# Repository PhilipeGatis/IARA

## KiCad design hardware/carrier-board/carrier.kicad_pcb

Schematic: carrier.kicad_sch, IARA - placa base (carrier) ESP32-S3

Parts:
BT1: CR2032; BatteryHolder_MYOUNG_BS-07-A1BJ001_CR2032; LCSC C2979167
C1: 470uF 25V; CP_Elec_10x10.5; LCSC C3445246
C2, C13, C16: 10uF 50V; C_1206_3216Metric; LCSC C13585
C3, C4, C9, C10, C14, C15, C17, C18, C19, C21, C22, C23, C24: 100nF; C_0603_1608Metric; LCSC C14663
C5, C6: 22uF 25V; C_1206_3216Metric; LCSC C12891
C7: 470uF 16V; CP_Elec_6.3x7.7; LCSC C2977552
C8: 1000uF 10V; CP_Elec_8x10.5; LCSC C48935400
C11, C12: 1uF; C_0603_1608Metric; LCSC C15849
C20: 100uF 16V; CP_Elec_6.3x5.4; LCSC C2887276
D1: SMBJ15A; D_SMB; LCSC C19077569
D2, D3, D5, D7, D9, D11, D13, D15, D17: SS34; D_SMA; LCSC C8678
D4, D6, D8, D10, D12, D14, D16, D18, D21: LED green; LED_0805_2012Metric; LCSC C2297
D19, D20, D22, D23: BAT54S; SOT-23; LCSC C7420333
F1, F2, F3, F4, F5, F6, F8, F9: PTC 0.75A hold; Fuse_1812_4532Metric; LCSC C369169
F7: PTC 0.5A hold; Fuse_1812_4532Metric; LCSC C369168
H1, H2, H3, H4: M3; MountingHole_3.2mm_M3
J1: 12V IN; TerminalBlock_Phoenix_MKDS-1,5-2-5.08_1x02_P5.08mm_Horizont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; LCSC C474952
J2: DevKit J1; PinSocket_1x22_P2.54mm_Vertical; LCSC C41376161
J3: DevKit J3; PinSocket_1x22_P2.54mm_Vertical; LCSC C41376161
J4: CH1 FERT1; TerminalBlock_Phoenix_PT-1,5-2-3.5-H_1x02_P3.50mm_Horizontal; LCSC C466970
J5: CH2 FERT2; TerminalBlock_Phoenix_PT-1,5-2-3.5-H_1x02_P3.50mm_Horizontal; LCSC C466970
J6: CH3 FERT3; TerminalBlock_Phoenix_PT-1,5-2-3.5-H_1x02_P3.50mm_Horizontal; LCSC C466970
J7: CH4 FERT4; TerminalBlock_Phoenix_PT-1,5-2-3.5-H_1x02_P3.50mm_Horizontal; LCSC C466970
J8: CH5 PRIME; TerminalBlock_Phoenix_PT-1,5-2-3.5-H_1x02_P3.50mm_Horizontal; LCSC C466970
J9: CH6 DRAIN; TerminalBlock_Phoenix_PT-1,5-2-3.5-H_1x02_P3.50mm_Horizontal; LCSC C466970
J10: CH7 REFILL; TerminalBlock_Phoenix_PT-1,5-2-3.5-H_1x02_P3.50mm_Horizontal; LCSC C466970
J11: CH8 SOLENOID; TerminalBlock_Phoenix_PT-1,5-2-3.5-H_1x02_P3.50mm_Horizontal; LCSC C466970
J12: REED; TerminalBlock_Phoenix_PT-1,5-2-3.5-H_1x02_P3.50mm_Horizontal; LCSC C466970
J13: SSR V SEL; PinHeader_1x03_P2.54mm_Vertical; LCSC C2894926
J14: SSR CANISTER; TerminalBlock_Phoenix_PT-1,5-3-3.5-H_1x03_P3.50mm_Horizontal; LCSC C474893
J15: CH9 PONTE H; TerminalBlock_Phoenix_PT-1,5-2-3.5-H_1x02_P3.50mm_Horizontal; LCSC C466970
J16: TFT ST7735; PinHeader_1x08_P2.54mm_Vertical; LCSC C492407
J17: BOTAO; PinHeader_1x02_P2.54mm_Vertical; LCSC C492401
J18: ULTRASSOM A02; PinHeader_1x04_P2.54mm_Vertical; LCSC C2691448
J19: BOIA; PinHeader_1x02_P2.54mm_Vertical; LCSC C492401
J20: I2C EXP; PinHeader_1x04_P2.54mm_Vertical; LCSC C2691448
L1: 4.7uH; L_Changjiang_FXL0630; LCSC C167220
Q1, Q2, Q3, Q4, Q5, Q6, Q7, Q8, Q9: AO3400A; SOT-23; LCSC C20917
Q10: AO4407A; SOIC-8_3.9x4.9mm_P1.27mm; LCSC C16072
R1, R4, R7, R10, R13, R16, R19, R22, R28, R37, R39, R41: 100R; R_0603_1608Metric; LCSC C22775
R2, R5, R8, R11, R14, R17, R20, R23, R25, R38, R40, R42, R48, R50, R53: 10k; R_0603_1608Metric; LCSC C25804
R3, R6, R9, R12, R15, R18, R21, R24, R33, R54, R55: 4.7k; R_0603_1608Metric; LCSC C23162
R26: 3.3k; R_0603_1608Metric; LCSC C22978
R27, R36, R47, R49, R51, R52: 1k; R_0603_1608Metric; LCSC C21190
R29: 470k; R_0603_1608Metric; LCSC C23178
R30: 47k; R_0603_1608Metric; LCSC C25819
R31, R43: 100k; R_0603_1608Metric; LCSC C25803
R32: 0.05R 1W; R_2512_6332Metric; LCSC C105390
R34: 22k; R_0603_1608Metric; LCSC C31850
R35: 6.8k; R_0603_1608Metric; LCSC C23212
R44: 0.5R 1/2W; R_1206_3216Metric; LCSC C859934
R45, R46: 33R; R_0603_1608Metric; LCSC C23140
TP1: +12V; TestPoint_THTPad_D1.5mm_Drill0.7mm
TP2: +5V; TestPoint_THTPad_D1.5mm_Drill0.7mm
TP3: +3V3; TestPoint_THTPad_D1.5mm_Drill0.7mm
TP4: GND; TestPoint_THTPad_D1.5mm_Drill0.7mm
U1: AP63205WU; TSOT-23-6; LCSC C2071056
U2, U4: INA219AIDR; SOIC-8_3.9x4.9mm_P1.27mm; LCSC C138706
U3: DRV8871DDAR; HTSOP-8-1EP_3.9x4.9mm_P1.27mm_EP2.4x3.2mm; LCSC C75864
U5: DS3231SN#; SOIC-16W_7.5x10.3mm_P1.27mm; LCSC C9866

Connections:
/+3V3: C8.1, C9.1, C14.1, C18.1, C20.1, C21.1, C23.1, D19.2 (K), D22.2 (K), D23.2 (K), J2.1, J2.2, J13.3, J16.1, J16.8, J18.1, J20.1, R48.1, R50.1, R53.1, R54.1, R55.1, TP3.1, U2.2 (A0), U2.5 (VS), U4.5 (VS), U5.2 (VCC)
/+5V: C5.1, C6.1, C7.1, D2.2 (A), J13.1, L1.2, TP2.1, U1.1 (FB)
/+5V_DK: D2.1 (K), J2.21
/+12V: C1.1, C2.1, C3.1, D1.1 (K), J1.1, Q10.1 (S), Q10.2 (S), Q10.3 (S), R31.1, TP1.1, U1.2 (EN), U1.3 (IN)
/+12V_PUMP: F1.1, F2.1, F3.1, F4.1, F5.1, F6.1, F7.1, F8.1, F9.1, R32.2, R33.1, R34.1, U2.7 (IN-)
/+12V_SW: C13.1, Q10.5 (D), Q10.6 (D), Q10.7 (D), Q10.8 (D), R32.1, U2.8 (IN+)
/BST5: C4.1, U1.6 (BST)
/BTN: C19.1, J2.15, R47.2, R48.2
/BTN_IN: J17.1, R47.1
/CAN_CTL: J2.12, R37.1
/CH1_CTL: J2.4, R1.1
/CH1_G: Q1.1 (G), R1.2, R2.1
/CH1_LED: D4.2 (A), R3.2
/CH1_NEG: D3.2 (A), D4.1 (K), J4.2, Q1.3 (D)
/CH1_POS: D3.1 (K), F1.2, J4.1, R3.1
/CH2_CTL: J2.5, R4.1
/CH2_G: Q2.1 (G), R4.2, R5.1
/CH2_LED: D6.2 (A), R6.2
/CH2_NEG: D5.2 (A), D6.1 (K), J5.2, Q2.3 (D)
/CH2_POS: D5.1 (K), F2.2, J5.1, R6.1
/CH3_CTL: J2.6, R7.1
/CH3_G: Q3.1 (G), R7.2, R8.1
/CH3_LED: D8.2 (A), R9.2
/CH3_NEG: D7.2 (A), D8.1 (K), J6.2, Q3.3 (D)
/CH3_POS: D7.1 (K), F3.2, J6.1, R9.1
/CH4_CTL: J2.7, R10.1
/CH4_G: Q4.1 (G), R10.2, R11.1
/CH4_LED: D10.2 (A), R12.2
/CH4_NEG: D9.2 (A), D10.1 (K), J7.2, Q4.3 (D)
/CH4_POS: D9.1 (K), F4.2, J7.1, R12.1
/CH5_CTL: J2.8, R13.1
/CH5_G: Q5.1 (G), R13.2, R14.1
/CH5_LED: D12.2 (A), R15.2
/CH5_NEG: D11.2 (A), D12.1 (K), J8.2, Q5.3 (D)
/CH5_POS: D11.1 (K), F5.2, J8.1, R15.1
/CH6_CTL: J2.9, R16.1
/CH6_G: Q6.1 (G), R16.2, R17.1
/CH6_LED: D14.2 (A), R18.2
/CH6_NEG: D13.2 (A), D14.1 (K), J9.2, Q6.3 (D)
/CH6_POS: D13.1 (K), F6.2, J9.1, R18.1
/CH7_CTL: J2.10, R19.1
/CH7_G: Q7.1 (G), R19.2, R20.1
/CH7_LED: D16.2 (A), R21.2
/CH7_NEG: D15.2 (A), D16.1 (K), J10.2, Q7.3 (D)
/CH7_POS: D15.1 (K), J10.1, J12.2, R21.1, R25.1
/CH8_CTL: J2.11, R22.1
/CH8_G: Q8.1 (G), R22.2, R23.1
/CH8_LED: D18.2 (A), R24.2
/CH8_NEG: D17.2 (A), D18.1 (K), J11.2, Q8.3 (D)
/CH8_POS: D17.1 (K), F8.2, J11.1, R24.1
/CH9_A: J15.1, R44.2, U4.7 (IN-)
/CH9_A_CTL: J3.17, R39.1
/CH9_B_CTL: J3.16, R41.1
/CH9_ILIM: R43.1, U3.4 (ILIM)
/CH9_IN1: R39.2, R40.1, U3.3 (IN1)
/CH9_IN2: R41.2, R42.1, U3.2 (IN2)
/CH9_OUT1: R44.1, U3.6 (OUT1), U4.8 (IN+)
/CH9_OUT2: J15.2, U3.8 (OUT2)
/CH9_VM: C16.1, C17.1, F9.2, U3.5 (VM)
/EN: J2.3, J16.4
/FLOAT: C22.1, D23.3 (COM), J3.6, R52.2, R53.2
/FLOAT_IN: J19.1, R52.1
/GND: BT1.2 (-), C1.2, C2.2, C3.2, C5.2, C6.2, C7.2, C8.2, C9.2, C10.2, C12.2, C13.2, C14.2, C15.2, C16.2, C17.2, C18.2, C19.2, C20.2, C21.2, C22.2, C23.2, C24.2, D1.2 (A), D19.1 (A), D20.1 (A), D21.1 (K), D22.1 (A), D23.1 (A), J1.2, J2.22, J3.1, J3.21, J3.22, J14.3, J16.2, J17.2, J18.2, J19.2, J20.2, Q1.2 (S), Q2.2 (S), Q3.2 (S), Q4.2 (S), Q5.2 (S), Q6.2 (S), Q7.2 (S), Q8.2 (S), Q9.2 (S), R2.2, R5.2, R8.2, R11.2, R14.2, R17.2, R20.2, R23.2, R26.2, R29.2, R35.2, R38.2, R40.2, R42.2, R43.2, TP4.1, U1.4 (GND), U2.1 (A1), U2.6 (GND), U3.1 (GND), U3.7 (GND), U3.9 (GND), U4.1 (A1), U4.2 (A0), U4.6 (GND), U5.5 (GND), U5.6 (GND), U5.7 (GND), U5.8 (GND), U5.9 (GND), U5.10 (GND), U5.11 (GND), U5.12 (GND), U5.13 (GND)
/HB: J2.20, R28.1
/HB_AC: C11.2, D20.3 (COM)
/HB_DC: C12.1, D20.2 (K), Q9.1 (G), R29.1
/HB_PULL: Q9.3 (D), R30.1
/HB_R: C11.1, R28.2
/I2C_SCL: J3.8, J20.4, R55.2, U2.4 (SCL), U4.4 (SCL), U5.16 (SCL)
/I2C_SDA: J3.9, J20.3, R54.2, U2.3 (SDA), U4.3 (SDA), U5.15 (SDA)
/PUMP_DIV: C15.1, R34.2, R35.1, R36.1
/PUMP_G: Q10.4 (G), R30.2, R31.2
/PUMP_LED: D21.2 (A), R33.2
/PUMP_SENSE: J3.18, R36.2
/REED_A: F7.2, J12.1
/REED_DIV: C10.1, D19.3 (COM), R25.2, R26.1, R27.1
/REED_SENSE: J3.7, R27.2
/SSR_SIG: J14.2, R37.2, R38.1
/SSR_V: J13.2, J14.1
/SW5: C4.2, L1.1, U1.5 (SW)
/TFT_CS: J2.16, J16.3
/TFT_DC: J2.19, J16.5
/TFT_MOSI: J16.6, R45.2
/TFT_MOSI_MCU: J2.17, R45.1
/TFT_SCK: J16.7, R46.2
/TFT_SCK_MCU: J2.18, R46.1
/US_RX: D22.3 (COM), J3.4, R49.2, R50.2
/US_RXI: J18.4, R51.2
/US_TX: J3.5, R51.1
/US_TXO: J18.3, R49.1
/VBAT: BT1.1 (+), C24.1, U5.14 (VBAT)

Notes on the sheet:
ENTRADA 12 V, PROTECAO E FONTE 5 V
Vem do fusivel T5A que ja existe na caixa
Surto e polaridade invertida: conduz e abre o fusivel T5A da caixa
Bootstrap
Impede que o 5 V da placa alimente a USB do PC
SOQUETE ESP32-S3-DevKitC-1
ESP32-S3-DevKitC-1, lado J1: 3V3 3V3 RST 4 5 6 7 15 16 17 18 8 3 46 9 10 11 12 13 14 5V GND
ESP32-S3-DevKitC-1, lado J3: GND TX RX 1 2 42 41 40 39 38 37 36 35 0 45 48 47 21 20 19 GND GND
Colado no soquete: correcao do brownout
CANAL 1
Pull-down: canal desligado no boot
Flyback na placa (o da ponta do fio continua)
Aceso = canal energizado
1 = +12V, 2 = retorno (MOSFET)
CANAL 2
CANAL 3
CANAL 4
CANAL 5
CANAL 6
CANAL 7 - RECALQUE + REED (trava de nivel maximo)
Reed NA em serie com o +12V do recalque
Divisor 12,5 V -> 3,1 V
CANAL 8
HEARTBEAT - CORTE DO 12V DAS BOMBAS SE O FIRMWARE TRAVAR + MONITOR DE CORRENTE
GPIO14: onda quadrada vinda do loop
So passa borda, nunca nivel parado
Bomba de carga: retifica as bordas
Sem borda por ~1 s: corta o 12V das bombas
Vgs = -8,5 V ligado, 0 V desligado
Chave geral do 12V dos 8 canais (P-MOSFET 30V 12A)
Shunt: 320 mV = 6,4 A, resolucao 0,2 mA
I2C 0x41: corrente total das bombas + tensao do 12V
Aceso = bombas habilitadas
GPIO21: firmware confere se o corte funciona
SSR DO CANISTER
Mantem o nivel do boot igual ao GPIO2 de hoje
Jumper: 1-2 = SSR de 5V, 2-3 = SSR de 3,3V
Borne: 1 = V+ do SSR, 2 = sinal, 3 = GND
CANAL 9 - PONTE H (eletrolise tipo Chihiros Doctor ou peristaltica reversivel)
GPIO47

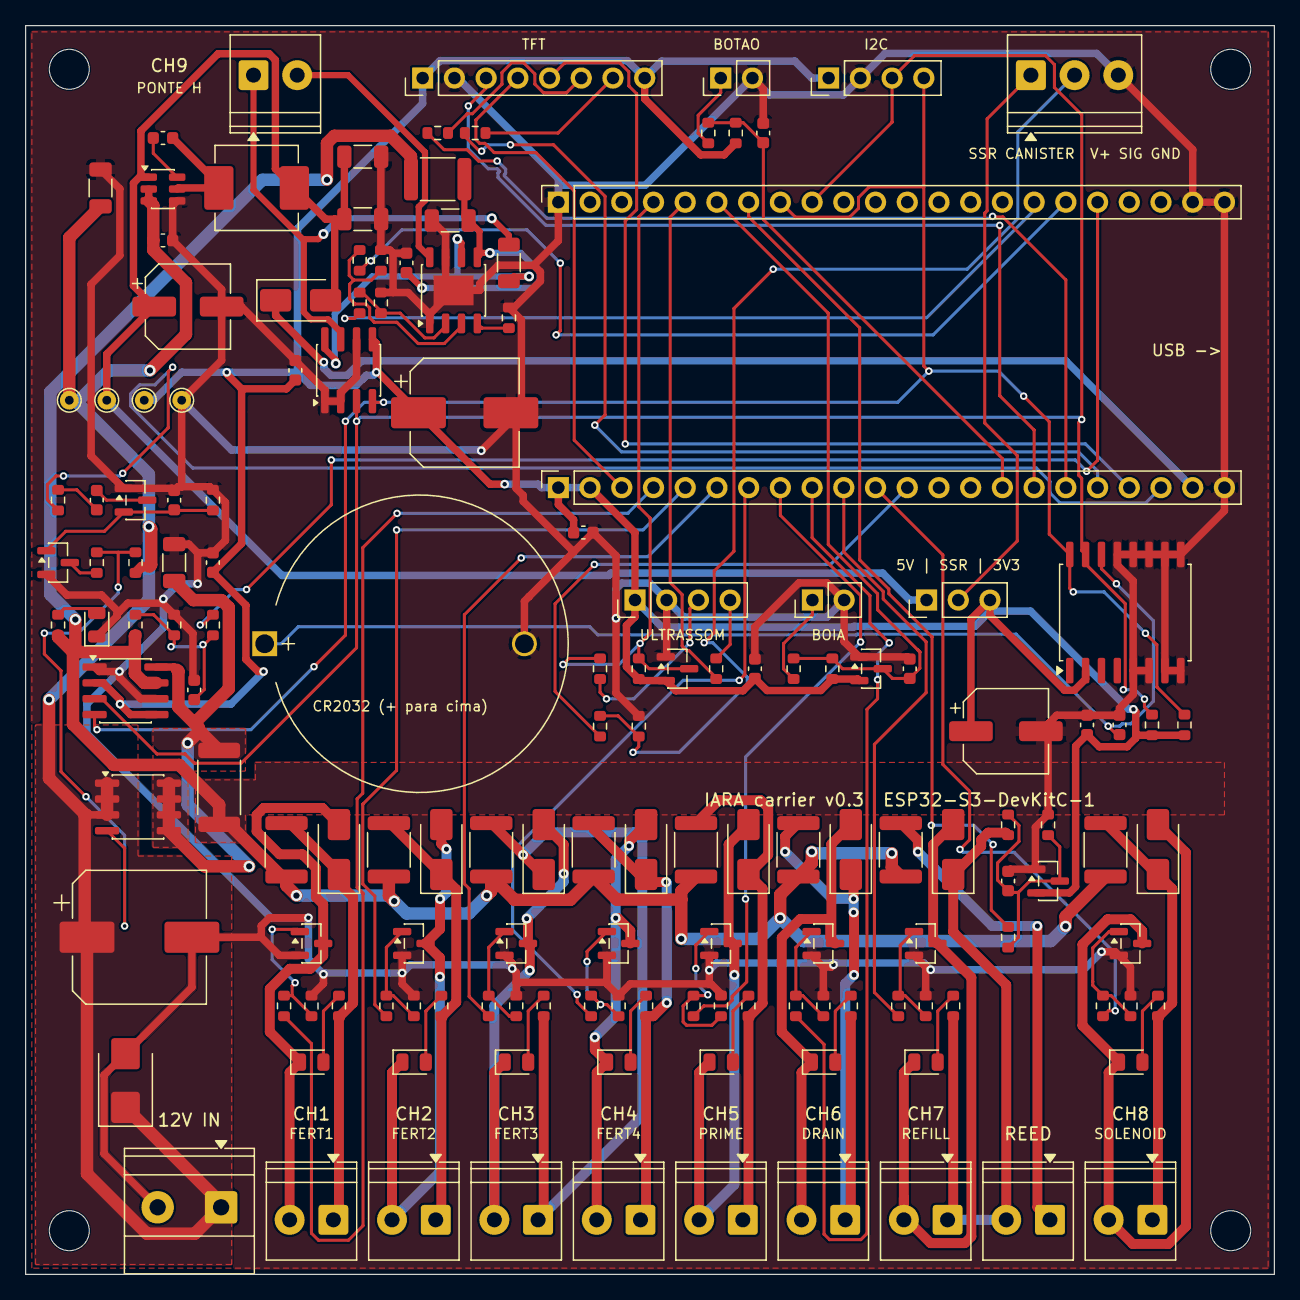
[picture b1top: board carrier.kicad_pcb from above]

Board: 2 copper layers, 100.0 x 100.0 mm, 156 parts (0 on the bottom side), 91 nets.

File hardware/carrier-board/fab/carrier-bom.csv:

Comment,Designator,Footprint,LCSC Part #
CR2032,BT1,BatteryHolder_MYOUNG_BS-07-A1BJ001_CR2032,C2979167
470uF 25V,C1,CP_Elec_10x10.5,C3445246
10uF 50V,"C2,C13,C16",C_1206_3216Metric,C13585
100nF,"C3,C4,C9,C10,C14,C15,C17,C18,C19,C21,C22,C23,C24",C_0603_1608Metric,C14663
22uF 25V,"C5,C6",C_1206_3216Metric,C12891
470uF 16V,C7,CP_Elec_6.3x7.7,C2977552
1000uF 10V,C8,CP_Elec_8x10.5,C48935400
1uF,"C11,C12",C_0603_1608Metric,C15849
100uF 16V,C20,CP_Elec_6.3x5.4,C2887276
SMBJ15A,D1,D_SMB,C19077569
SS34,"D2,D3,D5,D7,D9,D11,D13,D15,D17",D_SMA,C8678
LED green,"D4,D6,D8,D10,D12,D14,D16,D18,D21",LED_0805_2012Metric,C2297
BAT54S,"D19,D20,D22,D23",SOT-23,C7420333
PTC 0.75A hold,"F1,F2,F3,F4,F5,F6,F8,F9",Fuse_1812_4532Metric,C369169
PTC 0.5A hold,F7,Fuse_1812_4532Metric,C369168
12V IN,J1,"TerminalBlock_Phoenix_MKDS-1,5-2-5.08_1x02_P5.08mm_Horizontal",C474952
Conector C41376161,"J2,J3",PinSocket_1x22_P2.54mm_Vertical,C41376161
Borne parafuso 3.5mm 2P,"J4,J5,J6,J7,J8,J9,J10,J11,J12,J15","TerminalBlock_Phoenix_PT-1,5-2-3.5-H_1x02_P3.50mm_Horizontal",C466970
SSR V SEL,J13,PinHeader_1x03_P2.54mm_Vertical,C2894926
SSR CANISTER,J14,"TerminalBlock_Phoenix_PT-1,5-3-3.5-H_1x03_P3.50mm_Horizontal",C474893
TFT ST7735,J16,PinHeader_1x08_P2.54mm_Vertical,C492407
Conector C492401,"J17,J19",PinHeader_1x02_P2.54mm_Vertical,C492401
Conector C2691448,"J18,J20",PinHeader_1x04_P2.54mm_Vertical,C2691448
4.7uH,L1,L_Changjiang_FXL0630,C167220
AO3400A,"Q1,Q2,Q3,Q4,Q5,Q6,Q7,Q8,Q9",SOT-23,C20917
AO4407A,Q10,SOIC-8_3.9x4.9mm_P1.27mm,C16072
100R,"R1,R4,R7,R10,R13,R16,R19,R22,R28,R37,R39,R41",R_0603_1608Metric,C22775
10k,"R2,R5,R8,R11,R14,R17,R20,R23,R25,R38,R40,R42,R48,R50,R53",R_0603_1608Metric,C25804
4.7k,"R3,R6,R9,R12,R15,R18,R21,R24,R33,R54,R55",R_0603_1608Metric,C23162
3.3k,R26,R_0603_1608Metric,C22978
1k,"R27,R36,R47,R49,R51,R52",R_0603_1608Metric,C21190
470k,R29,R_0603_1608Metric,C23178
47k,R30,R_0603_1608Metric,C25819
100k,"R31,R43",R_0603_1608Metric,C25803
0.05R 1W,R32,R_2512_6332Metric,C105390
22k,R34,R_0603_1608Metric,C31850
6.8k,R35,R_0603_1608Metric,C23212
0.5R 1/2W,R44,R_1206_3216Metric,C859934
33R,"R45,R46",R_0603_1608Metric,C23140
AP63205WU,U1,TSOT-23-6,C2071056
INA219AIDR,"U2,U4",SOIC-8_3.9x4.9mm_P1.27mm,C138706
DRV8871DDAR,U3,HTSOP-8-1EP_3.9x4.9mm_P1.27mm_EP2.4x3.2mm,C75864
DS3231SN#,U5,SOIC-16W_7.5x10.3mm_P1.27mm,C9866

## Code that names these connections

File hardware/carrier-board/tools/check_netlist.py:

"""Project-specific checks on the exported netlist.

Run after `kicad-cli sch export netlist`. Each check states the rule it
enforces; a failure prints why and exits non-zero.
"""
import os
import sys

sys.path.insert(0, os.path.dirname(__file__))
from sexpr import find, find1, parse  # noqa: E402

path = sys.argv[1]
tree = parse(open(path).read())
nets = {}
values = {}
for c in find(find1(tree, "components"), "comp"):
    values[find1(c, "ref")[1]] = find1(c, "value")[1]
for n in find(find1(tree, "nets"), "net"):
    name = find1(n, "name")[1].lstrip("/")
    nets[name] = {(find1(x, "ref")[1], find1(x, "pin")[1]) for x in find(n, "node")}

fails = []


def check(cond, msg):
    print(("OK   " if cond else "FAIL ") + msg)
    if not cond:
        fails.append(msg)


def refs(net):
    return {r for r, _ in nets.get(net, ())}


def pin_net(ref, pin):
    for name, nodes in nets.items():
        if (ref, pin) in nodes:
            return name
    return None


# 1. Reed is the only path from the CH7 PTC to the refill pump.
reed = [r for r, v in values.items() if v == "REED"][0]
ch7 = [r for r, v in values.items() if v.startswith("CH7 ")][0]
check(len(nets["REED_A"]) == 2 and reed in refs("REED_A"),
      "REED_A liga so o PTC do CH7 e o borne do reed: %s" % sorted(nets["REED_A"]))
check(pin_net(ch7, "1") == "CH7_POS" and pin_net(reed, "2") == "CH7_POS",
      "o +12V do recalque (%s.1) so chega pelo reed (%s.2)" % (ch7, reed))
check(not (refs("+12V") & refs("CH7_POS")),
      "nenhum componente liga +12V direto ao CH7_POS")

# 2. Every gate has a pull-down and a series resistor.
for n in range(1, 9):
    g = "CH%d_G" % n
    rs = [r for r in refs(g) if r.startswith("R")]
    pd = [r for r in rs if values[r] == "10k" and r in refs("GND")]
    check(len(pd) == 1, "%s tem pull-down 10k para GND" % g)
    check(any(r in refs("CH%d_CTL" % n) for r in rs), "%s tem resistor serie vindo do GPIO" % g)

# 3. GPIO map on the DevKit socket (ESP32-S3-DevKitC-1 header order).
J1 = ["3V3", "3V3", "RST", 4, 5, 6, 7, 15, 16, 17, 18, 8, 3, 46, 9, 10, 11, 12, 13, 14, "5V", "GND"]
J3 = ["GND", 43, 44, 1, 2, 42, 41, 40, 39, 38, 37, 36, 35, 0, 45, 48, 47, 21, 20, 19, "GND", "GND"]
sock1 = [r for r, v in values.items() if v == "DevKit J1"][0]
sock3 = [r for r, v in values.items() if v == "DevKit J3"][0]
gpio = {}
for sock, order in ((sock1, J1), (sock3, J3)):
    for i, g in enumerate(order):
        net = pin_net(sock, str(i + 1))
        if isinstance(g, int) and net and not net.startswith("unconnected"):
            gpio[g] = net
print("     mapa GPIO -> rede:", ", ".join("GPIO%d=%s" % kv for kv in sorted(gpio.items())))
for strap in (0, 3, 45, 46):
    check(strap not in gpio, "GPIO%d (strapping) livre" % strap)
for psram in (35, 36, 37):
    check(psram not in gpio, "GPIO%d (PSRAM octal) livre" % psram)
for usb in (19, 20):
    check(usb not in gpio, "GPIO%d (USB) livre" % usb)
check(pin_net(sock1, "21") == "+5V_DK", "5V da DevKit vem pelo diodo (+5V_DK)")
check(len(refs("+5V_DK")) == 2, "+5V_DK liga so o diodo e o pino 5V")

# 4. Inputs from outside the box are clamped.
for net in ("FLOAT", "US_RX", "REED_DIV"):
    check(any(values[r] == "BAT54S" for r in refs(net)), "%s tem clamp BAT54S" % net)

# 5. Every channel has flyback and PTC.
for n in range(1, 9):
    pos, neg = "CH%d_POS" % n, "CH%d_NEG" % n
    check(any(values[r] == "SS34" for r in refs(pos) & refs(neg)), "CH%d tem flyback" % n)

# 6. Heartbeat: pump +12V only through the P-MOSFET, gated by a capacitor-coupled pulse.
ptcs = [r for r, v in values.items() if v.startswith("PTC")]
check(all(pin_net(r, "1") == "+12V_PUMP" for r in ptcs), "todos os PTCs dos canais saem do +12V_PUMP")
pfet = [r for r, v in values.items() if v == "AO4407A"][0]
check(pin_net(pfet, "1") == "+12V" and pin_net(pfet, "5") == "+12V_SW", "AO4407A liga +12V -> +12V_SW")
check(refs("+12V") & refs("+12V_SW") == {pfet}, "so o AO4407A une +12V e +12V_SW")
check(not (refs("+12V") & refs("+12V_PUMP")), "nada liga +12V direto no +12V_PUMP")
pshunt = [r for r, v in values.items() if v == "0.05R 1W"][0]
check(refs("+12V_SW") & refs("+12V_PUMP") == {pshunt} | {r for r in refs("+12V_SW") & refs("+12V_PUMP") if values[r] == "INA219AIDR"},
      "toda a corrente das bombas passa pelo shunt de 0,05R")
pmon = [r for r in refs("+12V_SW") if values[r] == "INA219AIDR"]
check(len(pmon) == 1 and pin_net(pmon[0], "8") == "+12V_SW" and pin_net(pmon[0], "7") == "+12V_PUMP"
      and pin_net(pmon[0], "2") == "+3V3" and pin_net(pmon[0], "1") == "GND",
      "INA219 das bombas le o shunt, endereco 0x41")
check(gpio.get(14) == "HB" and gpio.get(21) == "PUMP_SENSE", "GPIO14 = HB, GPIO21 = PUMP_SENSE")
hb_r = refs("HB_R")
check(len(hb_r) == 2 and all(values[r] in ("100R", "1uF") for r in hb_r),
      "HB chega ao retificador so por capacitor (nivel DC nao passa)")
check(any(values[r] == "470k" for r in refs("HB_DC") & refs("GND")), "HB_DC descarrega por 470k")

# 7. Channel 9 H-bridge: off at boot, fed from the heartbeat-gated rail, current measured.
drv = [r for r, v in values.items() if v == "DRV8871DDAR"][0]
ina = [r for r in refs("CH9_A") if values[r] == "INA219AIDR"][0]
check(gpio.get(47) == "CH9_A_CTL" and gpio.get(48) == "CH9_B_CTL", "GPIO47 = CH9 IN1, GPIO48 = CH9 IN2")
for net in ("CH9_IN1", "CH9_IN2"):
    check(any(values[r] == "10k" for r in refs(net) & refs("GND")), "%s tem pull-down (ponte parada no boot)" % net)
vm_ptc = [r for r in refs("CH9_VM") if values[r].startswith("PTC")]
check(pin_net(drv, "5") == "CH9_VM" and len(vm_ptc) == 1 and pin_net(vm_ptc[0], "1") == "+12V_PUMP",
      "DRV8871 VM vem do +12V_PUMP por PTC (heartbeat corta o canal 9)")
shunt = [r for r, v in values.items() if v.startswith("0.5R")][0]
check({pin_net(shunt, "1"), pin_net(shunt, "2")} == {"CH9_OUT1", "CH9_A"}
      and pin_net(ina, "8") == "CH9_OUT1" and pin_net(ina, "7") == "CH9_A",
      "INA219 le o shunt em serie com a saida A")
check(pin_net(ina, "1") == "GND" and pin_net(ina, "2") == "GND", "INA219 no endereco 0x40 (DS3231 fica em 0x68)")

# 8. No single-pin nets.
lonely = [n for n, nodes in nets.items() if len(nodes) < 2 and not n.startswith("unconnected")]
check(not lonely, "nenhuma rede com um pino so: %s" % lonely)

print("\n%d falha(s)" % len(fails))
sys.exit(1 if fails else 0)

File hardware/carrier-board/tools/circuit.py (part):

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# in reset or in the bootloader leaves HB_DC to bleed down through 470k (tau 0.47 s),
# the AO3400A turns off and the 100k pulls the P-MOSFET gate to its source.
B = "hb"
R("100R", "HB", "HB_R", B, note="GPIO14: onda quadrada vinda do loop")
C("1uF", "HB_R", "HB_AC", B, note="So passa borda, nunca nivel parado")
part("D", "Diode:BAT54S", "BAT54S", SOT23, {"A": "GND", "COM": "HB_AC", "K": "HB_DC"}, B,
     note="Bomba de carga: retifica as bordas")
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R("4.7k", "+12V_PUMP", "PUMP_LED", B)
part("D", "Device:LED", "LED green", "LED_SMD:LED_0805_2012Metric", {"A": "PUMP_LED", "K": "GND"}, B,
     note="Aceso = bombas habilitadas")
R("22k", "+12V_PUMP", "PUMP_DIV", B, note="GPIO21: firmware confere se o corte funciona")
R("6.8k", "PUMP_DIV", "GND", B)
C("100nF", "PUMP_DIV", "GND", B)
R("1k", "PUMP_DIV", "PUMP_SENSE", B)
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# ------------------------------------------------------------- canister SSR
B = "ssr"
R("100R", "CAN_CTL", "SSR_SIG", B)
R("10k", "SSR_SIG", "GND", B, note="Mantem o nivel do boot igual ao GPIO2 de hoje")
part("J", "Connector_Generic:Conn_01x03", "SSR V SEL", HDR % 3,
     {"1": "+5V", "2": "SSR_V", "3": "+3V3"}, B,
     note="Jumper: 1-2 = SSR de 5V, 2-3 = SSR de 3,3V")
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# The INA219 reads the signed load current over I2C (0x40), so the firmware
# can hold a set current in electrolysis mode and catch open/short loads.
B = "ch9"
R("100R", "CH9_A_CTL", "CH9_IN1", B, note="GPIO47")
R("10k", "CH9_IN1", "GND", B, note="Pull-down: ponte parada no boot")
R("100R", "CH9_B_CTL", "CH9_IN2", B, note="GPIO48 (o LED RGB da DevKit v1.1 fica no GPIO38)")
R("10k", "CH9_IN2", "GND", B)
part("F", "Device:Polyfuse", "PTC 0.75A hold", "Fuse:Fuse_1812_4532Metric",
     {"1": "+12V_PUMP", "2": "CH9_VM"}, B, note="Tambem cortado pelo heartbeat")
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
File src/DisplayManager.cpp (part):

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// CONSTRUCTOR
// =============================================================================
DisplayManager::DisplayManager()
    : _display(PIN_TFT_CS, PIN_TFT_DC, PIN_TFT_MOSI, PIN_TFT_SCK, PIN_TFT_RST),
      _time(nullptr), _water(nullptr), _fert(nullptr), _safety(nullptr),
      _web(nullptr), _currentPage(0), _lastPageSwitch(0), _lastRedraw(0),
      _bootLine(0), _btnLastState(true), _btnPressTs(0), _btnHandled(false),
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bool DisplayManager::initHardware() {
  // Button (skipped when disabled — D19 is used by the reservoir float switch)
  if (_btnEnabled()) {
    pinMode(PIN_BTN, INPUT_PULLUP);
  }

  _display.initR(INITR_BLACKTAB);
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    return;
  }

  bool btnNow = digitalRead(PIN_BTN); // LOW = pressed (active low)
  unsigned long now = millis();

  // Detect press edge (HIGH → LOW)
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void DisplayManager::_drawHeaderLevelBar() {
  _display.setTextSize(1); // reset — previous page may have set size 3
  float dist = _safety->getLastDistance();
  const float maxDist = 30.0f;
  uint8_t barX = 80;
  uint8_t barW = 70;
  uint8_t barH = 10;
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// =============================================================================
// WATER LEVEL PERCENTAGE (DRY #2)
// =============================================================================
float DisplayManager::_calcWaterPct(float distCm) const {
  float sf = (float)_web->getSensorFullDistanceMm() / 10.0f;
  float refCm = (_web->getAqHeight() > 0) ? (float)_web->getAqHeight() : 20.0f;
  float pct = 100.0f - (((distCm - sf) / refCm) * 100.0f);
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
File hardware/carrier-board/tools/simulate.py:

"""SPICE checks of the carrier board's safety-relevant sub-circuits.

Drives KiCad's bundled libngspice through ctypes, so nothing extra needs
installing. Component values are copied from circuit.py; MOSFET models are
level-1 fits to the datasheet R_DS(on) points, run at typical and worst-case
threshold. Writes PNG plots to ../sim/ and prints a pass/fail line per check.

    python3 tools/simulate.py
"""
import ctypes
import os
import sys

import matplotlib
matplotlib.use("Agg")
import matplotlib.pyplot as plt  # noqa: E402

HERE = os.path.dirname(os.path.abspath(__file__))
OUT = os.path.join(HERE, "..", "sim")
LIB = "/Applications/KiCad/KiCad.app/Contents/Frameworks/libngspice.0.dylib"
VIN = 12.53  # measured supply

os.makedirs(OUT, exist_ok=True)
ng = ctypes.CDLL(LIB)
_log = []
PRINTF = ctypes.CFUNCTYPE(ctypes.c_int, ctypes.c_char_p, ctypes.c_int, ctypes.c_void_p)
STAT = ctypes.CFUNCTYPE(ctypes.c_int, ctypes.c_char_p, ctypes.c_int, ctypes.c_void_p)
EXIT = ctypes.CFUNCTYPE(ctypes.c_int, ctypes.c_int, ctypes.c_bool, ctypes.c_bool, ctypes.c_int, ctypes.c_void_p)
_cb = (PRINTF(lambda s, i, p: _log.append(s.decode(errors="replace")) or 0),
       STAT(lambda s, i, p: 0), EXIT(lambda *a: 0))
ng.ngSpice_Init(_cb[0], _cb[1], _cb[2], None, None, None, None)

MODELS = """
.model BAT54 D(Is=2e-7 N=1.04 Rs=2.4 Cjo=10p Bv=30 Ibv=100u)
.model SS34 D(Is=5e-5 N=1.1 Rs=0.03 Cjo=200p Bv=40)
* AO3400A: Rds(on) 48 mOhm @ Vgs 2.5 V, 33 mOhm @ 4.5 V
.model AO3400A NMOS(Level=1 Vto={VTN} Kp=14 Lambda=0.01 Cgso=400p Cgdo=60p)
* AO4407A: Rds(on) ~14 mOhm @ Vgs -10 V
.model AO4407A PMOS(Level=1 Vto=-1.9 Kp=12 Lambda=0.01 Cgso=2.2n Cgdo=300p)
"""


def run(netlist, vectors):
    """Load a netlist, run it, return {vector: [values]} including the scale."""
    lines = ["* sim"] + netlist.strip().splitlines() + MODELS.strip().splitlines() + [".end"]
    arr = (ctypes.c_char_p * (len(lines) + 1))(*[l.encode() for l in lines], None)
    ng.ngSpice_Command(b"remcirc")
    ng.ngSpice_Circ(arr)
    ng.ngSpice_Command(b"run")
    path = os.path.join(OUT, "_tmp.txt")
    ng.ngSpice_Command(("wrdata %s %s" % (path, " ".join(vectors))).encode())
    data = {"x": []}
    for v in vectors:
        data[v] = []
    for row in open(path):
        cols = [float(c) for c in row.split()]
        if not cols:
            continue
        data["x"].append(cols[0])
        for i, v in enumerate(vectors):
            data[v].append(cols[2 * i + 1])
    os.remove(path)
    return data


results = []


def check(ok, msg):
    results.append(ok)
    print(("OK   " if ok else "FAIL ") + msg)


def first_cross(xs, ys, level, rising, after=0.0):
    for x, a, b in zip(xs[1:], ys, ys[1:]):
        if x > after and ((rising and a < level <= b) or (not rising and a > level >= b)):
            return x
    return None


# ----------------------------------------------------------------- 1. heartbeat
def heartbeat(freq, stop_at, vtn, tag):
    """GPIO14 toggles at `freq` Hz until `stop_at`, then holds high forever."""
    half = 0.5 / freq
    pts, t, lvl = ["0 0"], 0.0, 0.0
    while t + half < stop_at:
        t += half
        pts.append("%.6f %.1f" % (t, lvl))
        lvl = 3.3 - lvl
        pts.append("%.6f %.1f" % (t + 1e-6, lvl))
    pts.append("%.6f 3.3" % (t + 2e-6))
    net = """
.param VTN=%g
VIN vin 0 %g
VHB hb_src 0 PWL(%s)
RGPIO hb_src hb 25
R28 hb hb_r 100
C11 hb_r hb_ac 1u
DCL 0 hb_ac BAT54
DRC hb_ac hb_dc BAT54
C12 hb_dc 0 1u
R29 hb_dc 0 470k
M9 pull hb_dc 0 0 AO3400A
R30 pull pg 47k
R31 vin pg 100k
M10 pump pg vin vin AO4407A
C13 pump 0 10u
RLOAD pump 0 12
.tran 0.05m %g 0 0.05m
""" % (vtn, VIN, " ".join(pts), stop_at + 3.0)
    d = run(net, ["v(hb)", "v(hb_dc)", "v(pg)", "v(pump)"])
    on = first_cross(d["x"], d["v(pump)"], 0.9 * VIN, True)
    off = first_cross(d["x"], d["v(pump)"], 1.0, False, after=stop_at)
    steady = [v for x, v in zip(d["x"], d["v(pump)"]) if stop_at - 0.5 < x < stop_at]
    fig, ax = plt.subplots(3, 1, figsize=(10, 7), sharex=True)
    ax[0].plot(d["x"], d["v(hb)"], lw=0.5)
    ax[0].set_ylabel("GPIO14 (V)")
    ax[1].plot(d["x"], d["v(hb_dc)"], color="tab:orange")
    ax[1].axhline(vtn, ls="--", color="grey", lw=0.8)
    ax[1].set_ylabel("HB_DC (V)")
    ax[2].plot(d["x"], d["v(pump)"], color="tab:green")
    ax[2].set_ylabel("+12V_PUMP (V)")
    ax[2].set_xlabel("tempo (s)")
    for a in ax:
        a.axvline(stop_at, color="red", lw=0.8)
        a.grid(alpha=0.3)
    ax[0].set_title("Heartbeat %s: pisca a %g Hz ate %.0f s, depois trava em HIGH (linha vermelha)" % (tag, freq, stop_at))
    fig.tight_layout()
    fig.savefig(os.path.join(OUT, "heartbeat-%s.png" % tag), dpi=110)
    plt.close(fig)
    return on, off, (min(steady) if steady else 0.0)


print("\n1. HEARTBEAT (corte do 12V das bombas)")
for vtn, tag in ((1.05, "tipico"), (1.45, "pior-vth-alto"), (0.65, "pior-vth-baixo")):
    on, off, vmin = heartbeat(25, 3.0, vtn, tag)
    off_s = (off - 3.0) if off else None
    print("     Vth %.2f V: liga em %s, 12V_PUMP minimo pulsando %.2f V, corta %s apos travar" % (
        vtn, "%.0f ms" % (on * 1e3) if on else "NUNCA", vmin,
        "%.2f s" % off_s if off_s is not None else "NUNCA"))
    check(on is not None and on < 1.0, "Vth %.2f: bombas habilitam em menos de 1 s" % vtn)
    check(vmin > 0.95 * VIN, "Vth %.2f: 12V_PUMP estavel enquanto pisca (sem queda > 5%%)" % vtn)
    check(off_s is not None and off_s < 5.0, "Vth %.2f: corta em menos de 5 s com o GPIO parado" % vtn)

# a blocked loop that still toggles slowly must not hold the rail
on, off, vmin = heartbeat(1, 6.0, 1.05, "lento-1Hz")
check(vmin < 0.5 * VIN or on is None, "piscando a 1 Hz (loop travado) o 12V_PUMP nao se mantem: min %.2f V" % vmin)

# -------------------------------------------------------- 2. sense dividers
print("\n2. DIVISORES DE LEITURA (reed GPIO41, bombas GPIO21)")
for v12 in (VIN, 15.0):
    net = """
VIN v12 0 %g
V33 v33 0 3.3
R10 v12 reed_div 10k
R11 reed_div 0 3.3k
DA 0 reed_div BAT54
DK reed_div v33 BAT54
R12 reed_div gpio41 1k
RIN41 gpio41 0 10Meg
R33 v12 pump_div 22k
R34 pump_div 0 6.8k
R35 pump_div gpio21 1k
RIN21 gpio21 0 10Meg
.op
""" % v12
    lines = ["* op"] + net.strip().splitlines() + MODELS.replace("{VTN}", "1").strip().splitlines() + [".end"]
    arr = (ctypes.c_char_p * (len(lines) + 1))(*[l.encode() for l in lines], None)
    ng.ngSpice_Command(b"remcirc")
    ng.ngSpice_Circ(arr)
    ng.ngSpice_Command(b"run")
    _log.clear()
    ng.ngSpice_Command(b"print v(gpio41) v(gpio21)")
    vals = {}
    for l in _log:
        l = l.replace("stdout", "").strip()
        if "=" in l:
            k, v = l.split("=")
            vals[k.strip()] = float(v)
    g41, g21 = vals.get("v(gpio41)", 0), vals.get("v(gpio21)", 0)
    print("     12V = %.2f V: GPIO41 (reed) = %.2f V, GPIO21 (bombas) = %.2f V" % (v12, g41, g21))
    check(2.475 <= g41 <= 3.6, "reed com %.2f V: le HIGH com folga e abaixo do maximo do ESP (3,6 V)" % v12)
    check(2.475 <= g21 <= 3.6, "sensor de bombas com %.2f V: le HIGH e abaixo de 3,6 V" % v12)

# ------------------------------------------------- 3. channel gate + flyback
print("\n3. CANAL DE BOMBA (gate 3,3 V, PWM 5 kHz, flyback)")
for vtn, tag in ((1.05, "tipico"), (1.45, "pior")):
    net = """
.param VTN=%g
VIN vin 0 %g
VG g_src 0 PULSE(0 3.3 0 20n 20n 100u 200u)
RGPIO g_src ctl 25
R100 ctl g 100
R10K g 0 10k
RPTC vin pos 0.15
LPUMP pos m 1m
RPUMP m neg 16
DFLY neg pos SS34
M1 neg g 0 0 AO3400A
.tran 0.1u 4m 2m 0.05u
""" % (vtn, VIN)
    d = run(net, ["v(g)", "v(neg)", "i(vin)"])
    on_samples = sorted(v for v, g in zip(d["v(neg)"], d["v(g)"]) if g > 3.2)
    vds_on = on_samples[len(on_samples) // 2]  # median while the gate is fully on
    vpk = max(d["v(neg)"])
    i_pk = max(-i for i in d["i(vin)"])
    fig, ax = plt.subplots(2, 1, figsize=(10, 5), sharex=True)
    ax[0].plot([x * 1e3 for x in d["x"]], d["v(g)"])
    ax[0].set_ylabel("gate (V)")
    ax[1].plot([x * 1e3 for x in d["x"]], d["v(neg)"], color="tab:red")
    ax[1].set_ylabel("dreno (V)")
    ax[1].set_xlabel("tempo (ms)")
    ax[0].set_title("Canal de bomba, Vth %.2f V: PWM 5 kHz 50%%, bomba 16 ohm + 1 mH" % vtn)
    for a in ax:
        a.grid(alpha=0.3)
    fig.tight_layout()
    fig.savefig(os.path.join(OUT, "canal-%s.png" % tag), dpi=110)
    plt.close(fig)
    i_on = (VIN - vds_on) / 16.15
    print("     Vth %.2f V: Vds ligado %.0f mV (~%.0f mOhm), pico no dreno %.2f V, corrente de pico %.2f A" % (
        vtn, vds_on * 1e3, vds_on / max(i_on, 1e-3) * 1e3, vpk, i_pk))
    check(vds_on < 0.1, "Vth %.2f: MOSFET satura com 3,3 V no gate (Vds < 100 mV)" % vtn)
    check(vpk < VIN + 1.5, "Vth %.2f: flyback segura o pico no desligamento (< %.1f V, AO3400A aguenta 30 V)" % (vtn, VIN + 1.5))

print("\n%d de %d checagens OK. Graficos em %s" % (sum(results), len(results), os.path.abspath(OUT)))
sys.exit(0 if all(results) else 1)
